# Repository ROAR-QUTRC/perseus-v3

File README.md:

# perseus-v3

The code base for the QUT Robotics Club ROAR teams rover Perseus starting 2026

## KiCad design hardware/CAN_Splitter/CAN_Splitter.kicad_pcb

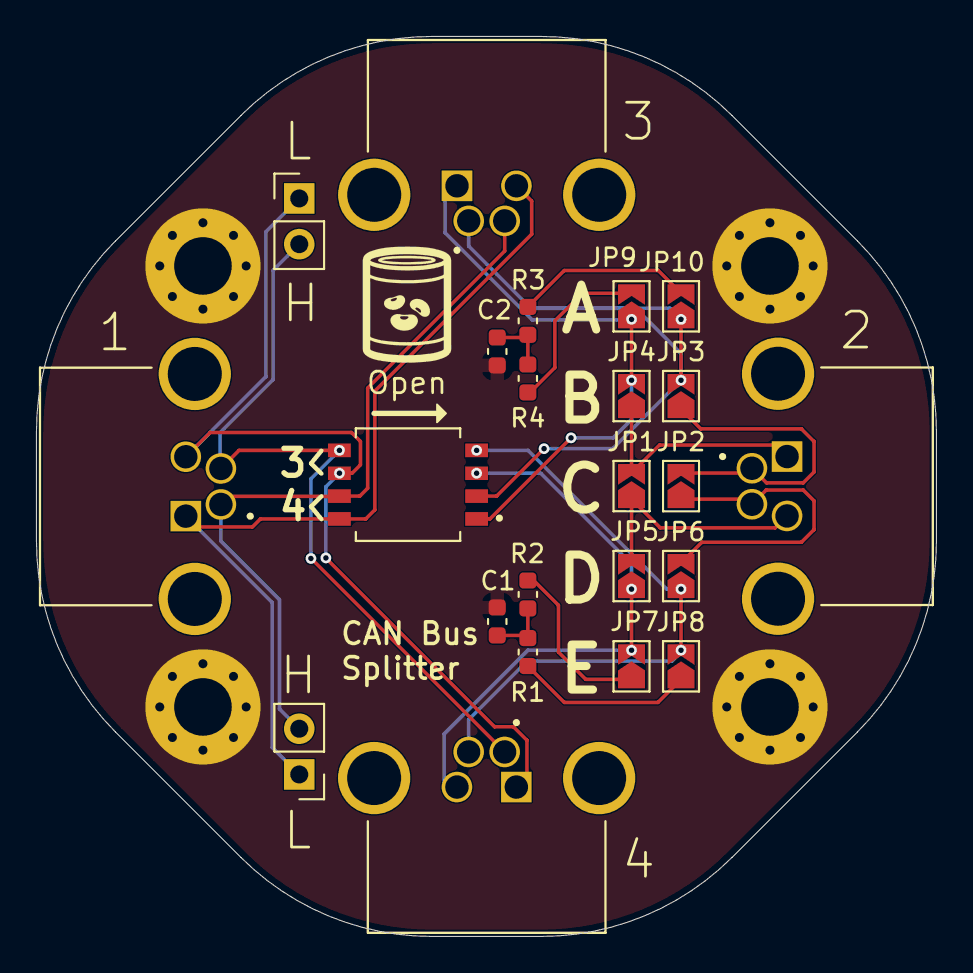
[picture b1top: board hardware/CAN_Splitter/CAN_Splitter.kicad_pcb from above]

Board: 2 copper layers, 50.0 x 50.0 mm, 27 parts (0 on the bottom side), 19 nets.

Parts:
C1, C2: 4.7nF; C_0603_1608Metric
H1, H2, H3, H4: MountingHole_Pad; MountingHole_3.2mm_M3_Pad_Via
J1, J2, J3, J4: 54-00274; TENSILITY_54-00274
J5, J6: Conn_01x02; PinHeader_1x02_P2.54mm_Vertical
JP1, JP2, JP3, JP4, JP5, JP6, JP7, JP8, JP9, JP10: SolderJumper_2_Open; SolderJumper-2_P1.3mm_Open_TrianglePad1.0x1.5mm
R1, R2, R3, R4: 62R; C_0603_1608Metric
SW1: SW_DIP_x04; SW_218-4LPSTR

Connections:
/1 A High: J1.2, J3.4, J5.2, SW1.7
/1 A Low: J1.1, J3.3, J5.1, SW1.8
/1 B High: J1.4, J4.2, J6.2, SW1.5
/1 B Low: J1.3, J4.1, J6.1, SW1.6
/2 A High: J2.2, JP2.2 (B), JP3.1 (A)
/2 A Low: J2.1, JP1.2 (B), JP4.1 (A)
/2 B High: J2.4, JP2.1 (A), JP6.2 (B)
/2 B Low: J2.3, JP1.1 (A), JP5.2 (B)
GND: C1.2, C2.2, H1.1 (1_1), H2.1 (1_1), H3.1 (1_1), H4.1 (1_1)
unnamed: C1.1, R1.1, R2.1
unnamed: C2.1, R3.1, R4.1
unnamed: J3.1, JP4.2 (B), JP9.1 (A), SW1.1
unnamed: J4.3, JP5.1 (A), JP7.2 (B), SW1.3
unnamed: J4.4, JP6.1 (A), JP8.2 (B), SW1.4
unnamed: JP7.1 (A), R2.2
unnamed: JP8.1 (A), R1.2
unnamed: JP9.2 (B), R4.2
unnamed: J3.2, JP3.2 (B), JP10.1 (A), SW1.2
unnamed: JP10.2 (B), R3.2

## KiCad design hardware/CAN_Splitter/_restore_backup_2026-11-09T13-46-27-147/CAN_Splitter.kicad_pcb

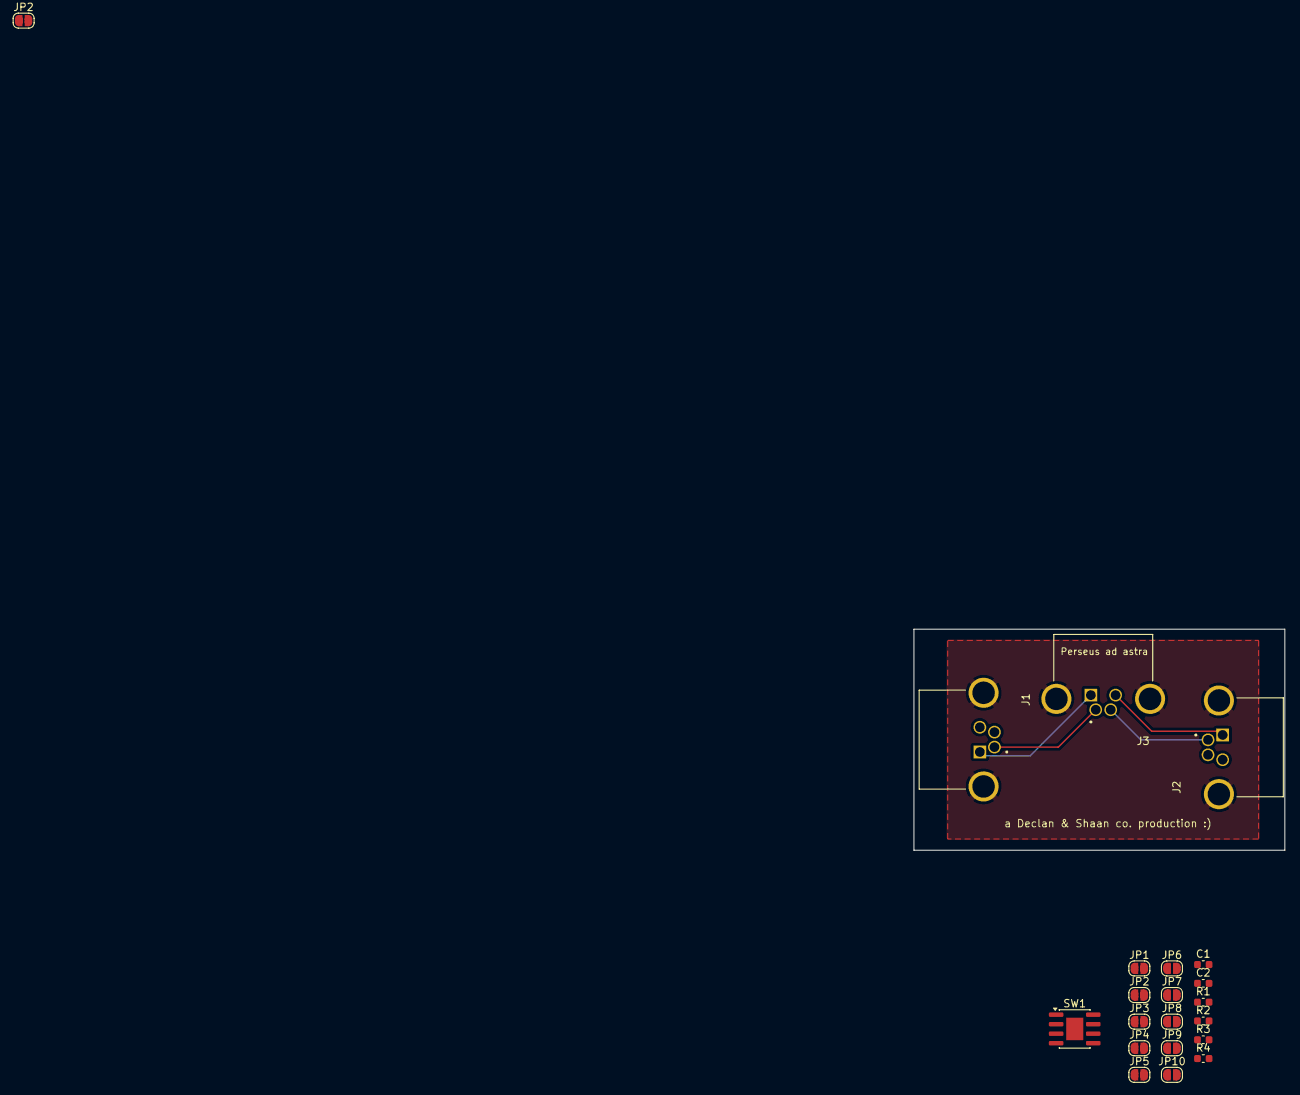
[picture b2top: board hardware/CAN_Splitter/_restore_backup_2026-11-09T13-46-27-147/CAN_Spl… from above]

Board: 2 copper layers, 49.5 x 29.5 mm, 21 parts (0 on the bottom side), 19 nets.

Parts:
C1, C2: 4.7nF; C_0603_1608Metric
J1, J2, J3: 54-00274; TENSILITY_54-00274
JP1, JP2, JP2#2, JP3, JP4, JP5, JP6, JP7, JP8, JP9, JP10: SolderJumper_2_Open; SolderJumper-2_P1.3mm_Open_RoundedPad1.0x1.5mm
R1, R2, R3, R4: 62R; C_0603_1608Metric
SW1: SW_DIP_x04; SOIC-8-1EP_3.9x4.9mm_P1.27mm_EP2.29x3mm

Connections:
/A High: J1.2, J3.4, SW1.2
/A Low: J1.1, J3.3, SW1.1
/B High: J1.4, SW1.4
/B Low: J1.3, SW1.3
GND: C1.2, C2.2, J1.S1 (SHIELD), J1.S2 (SHIELD), J2.S1 (SHIELD), J2.S2 (SHIELD), J3.S1 (SHIELD), J3.S2 (SHIELD)
unnamed: C1.1, R1.1, R2.1
unnamed: C2.1, R3.1, R4.1
unnamed: JP1.1 (A), JP5.1 (A)
unnamed: JP1.2 (B), JP4.1 (A)
unnamed: JP2.1 (A), JP2#2.1 (A), JP6.1 (A)
unnamed: JP2.2 (B), JP2#2.2 (B), JP3.1 (A)
unnamed: J3.1, JP4.2 (B), JP9.2 (B), SW1.8
unnamed: JP5.2 (B), JP7.2 (B), SW1.6
unnamed: JP6.2 (B), JP8.2 (B), SW1.5
unnamed: JP7.1 (A), R2.2
unnamed: JP8.1 (A), R1.2
unnamed: JP9.1 (A), R4.2
unnamed: JP10.1 (A), R3.2
unnamed: J3.2, JP3.2 (B), JP10.2 (B), SW1.7

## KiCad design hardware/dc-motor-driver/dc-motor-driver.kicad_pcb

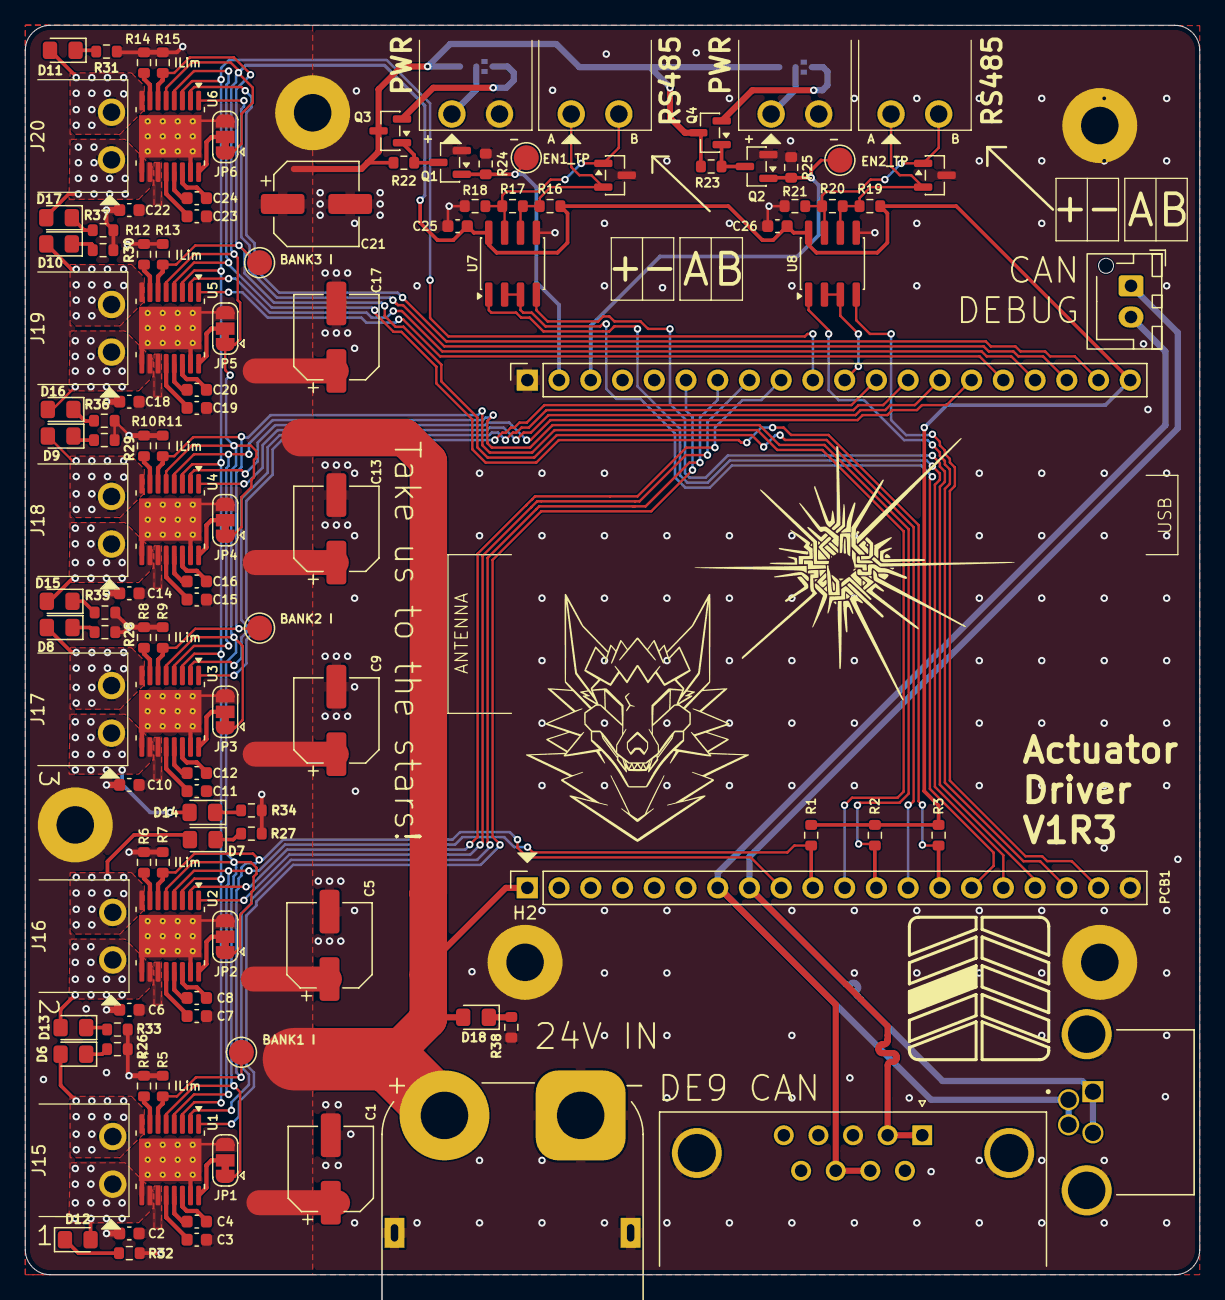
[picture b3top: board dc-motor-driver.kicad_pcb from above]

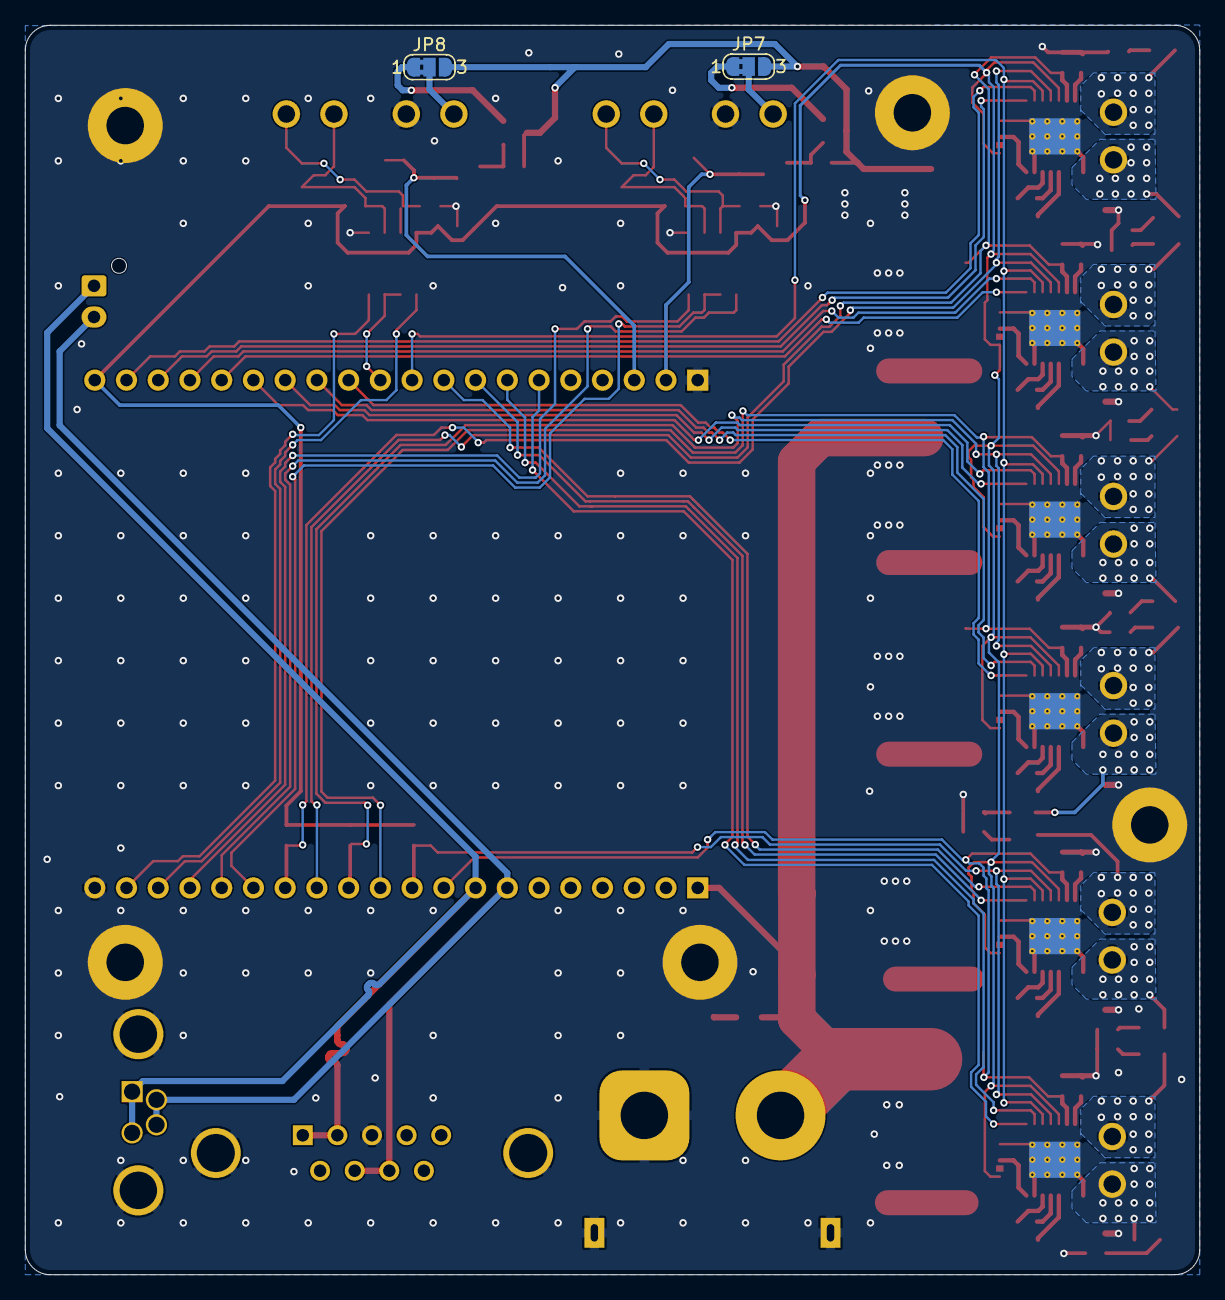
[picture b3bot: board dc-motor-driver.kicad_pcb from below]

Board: 2 copper layers, 94.0 x 100.0 mm, 124 parts (2 on the bottom side), 97 nets.

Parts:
C1, C5, C9, C13, C17, C21: 100u; CP_Elec_6.3x7.7
C2, C3, C6, C7, C10, C11, C14, C15, C18, C19, C22, C23, C25, C26: 100n; C_0603_1608Metric
C4, C8, C12, C16, C20, C24: 22n; C_0603_1608Metric
D1, D2: SM712_SOT23; SOT-23
D6, D7, D8, D9, D10, D11, D12, D13, D14, D15, D16, D17, D18: GREEN; LED_0805_2012Metric_Pad1.15x1.40mm_HandSolder
H1, H2, H3, H4, H5: MountingHole_Pad; MountingHole_3mm_Pad
J1: Tensility_M8_Socket_4P_Shielded_A
J2: VIN; AMASS_XT90PW-M_1x02_P10.90mm_Horizontal
J3: DE9; A-DF_09_A_KG-T2S
J4: Conn_01x02; JST_XH_B2B-XH-AM_1x02_P2.50mm_Vertical
J10, J11, J12, J13, J15, J16, J17, J18, J19, J20: OQ0232510000G; AnyTek_OQ_3.81mm_90_2P_TriangleKeyLock
JP1, JP2, JP3, JP4, JP5, JP6: Jumper_3_Bridged12; SolderJumper-3_P1.3mm_Bridged12_RoundedPad1.0x1.5mm
JP7, JP8: Jumper_3_Bridged12; SolderJumper-3_P1.3mm_Bridged2Bar12_RoundedPad1.0x1.5mm_Num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
PCB1: Smol Brain Board; Smol_Brain_Board
Q1, Q2: 2N7002; SOT-23
Q3, Q4: Si2371EDS; SOT-23
R1, R2, R3, R22, R23, R24, R25, R26, R27, R28, R29, R30, R31, R32, R33, R34, R35, R36, R37, R38: 10k; R_0603_1608Metric
R4, R6, R8, R10, R12, R14: 20k; R_0603_1608Metric
R5, R7, R9, R11, R13, R15: 1k3; R_0603_1608Metric
R16, R18, R19, R21: 330; R_0603_1608Metric
R17, R20: 120; R_0603_1608Metric
TP1, TP2, TP3, TP4, TP5: TestPoint; TestPoint_Pad_D2.0mm
U1, U2, U3, U4, U5, U6: DRV8874PWPR; HTSSOP-16-1EP_4.4x5mm_P0.65mm_EP3.4x5mm_Mask2.66x2.46mm_The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
U7, U8: SP3485CN; SOIC-8_3.9x4.9mm_P1.27mm

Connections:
+3V3: C25.1, C26.1, JP1.1 (A), JP2.1 (A), JP3.1 (A), JP4.1 (A), JP5.1 (A), JP6.1 (A), PCB1.21 (3V3), R1.2, R2.2, R3.2, R16.1, R19.1, U1.5 (VREF), U2.5 (VREF), U3.5 (VREF), U4.5 (VREF), U5.5 (VREF), U6.5 (VREF), U7.8 (VCC), U8.8 (VCC)
/BANK1_I_SENSE: PCB1.9 (A1), R5.1, R7.1, TP1.1 (1_1), U1.6 (IPROPI), U2.6 (IPROPI)
/BANK1_~FLT: PCB1.10 (A2), R1.1, U1.4 (~FAULT), U2.4 (~FAULT)
/BANK2_I_SENSE: PCB1.11 (A3), R9.1, R11.1, TP2.1 (1_1), U3.6 (IPROPI), U4.6 (IPROPI)
/BANK2_~FLT: PCB1.12 (A4), R2.1, U3.4 (~FAULT), U4.4 (~FAULT)
/BANK3_I_SENSE: PCB1.13 (A5), R13.1, R15.1, TP3.1 (1_1), U5.6 (IPROPI), U6.6 (IPROPI)
/BANK3_~FLT: PCB1.14 (A6), R3.1, U5.4 (~FAULT), U6.4 (~FAULT)
/CAN+: J1.2, J1.4, J3.7, J3.8, J4.2, PCB1.7 (CAN_H)
/CAN-: J1.1, J1.3, J3.1, J3.2, J4.1, PCB1.8 (CAN_L)
/ENC_PWR_SW_1: PCB1.39 (I2C_SCK), Q1.1 (G), R24.1, TP4.1 (1_1)
/ENC_PWR_SW_2: PCB1.38 (I2C_SDA), Q2.1 (G), R25.1, TP5.1 (1_1)
/MCU1_DIR: PCB1.15 (A7), U7.2 (~RE), U7.3 (DE)
/MCU1_RX: PCB1.16 (A8), U7.1 (RO)
/MCU1_TX: PCB1.17 (A9), U7.4 (DI)
/MCU2_DIR: PCB1.30 (IO39), U8.2 (~RE), U8.3 (DE)
/MCU2_RX: PCB1.18 (A10), U8.1 (RO)
/MCU2_TX: PCB1.19 (IO12), U8.4 (DI)
/MOT1_IN1: PCB1.35 (IO15), U1.1 (EN_IN1)
/MOT1_IN2: PCB1.34 (IO16), U1.2 (PH_IN2)
/MOT2_IN1: PCB1.33 (IO42), U2.1 (EN_IN1)
/MOT2_IN2: PCB1.32 (IO41), U2.2 (PH_IN2)
/MOT3_IN1: PCB1.29 (IO38), U3.1 (EN_IN1)
/MOT3_IN2: PCB1.28 (IO37), U3.2 (PH_IN2)
/MOT4_IN1: PCB1.27 (IO45), U4.1 (EN_IN1)
/MOT4_IN2: PCB1.26 (IO48), U4.2 (PH_IN2)
/MOT5_IN1: PCB1.25 (IO47), U5.1 (EN_IN1)
/MOT5_IN2: PCB1.24 (IO21), U5.2 (PH_IN2)
/MOT6_IN1: PCB1.23 (IO14), U6.1 (EN_IN1)
/MOT6_IN2: PCB1.22 (IO13), U6.2 (PH_IN2)
/~SLEEP: PCB1.31 (IO40), U1.3 (~SLEEP), U2.3 (~SLEEP), U3.3 (~SLEEP), U4.3 (~SLEEP), U5.3 (~SLEEP), U6.3 (~SLEEP)
GND: C1.2, C2.2, C5.2, C6.2, C9.2, C10.2, C13.2, C14.2, C17.2, C18.2, C21.2, C22.2, C25.2, C26.2, D1.3 (common), D2.3 (common), H1.1 (1_1), H2.1 (1_1), H3.1 (1_1), H4.1 (1_1), H5.1 (1_1), J1.S1 (SHIELD), J1.S2 (SHIELD__1), J2.1 (-), J2.MP, J3.0 (PAD), J3.3, J10.2, J12.2, JP1.3 (B), JP2.3 (B), JP3.3 (B), JP4.3 (B), JP5.3 (B), JP6.3 (B), PCB1.20 (GND), PCB1.40 (GND), Q1.2 (S), Q2.2 (S), R4.2, R5.2, R6.2, R7.2, R8.2, R9.2, R10.2, R11.2, R12.2, R13.2, R14.2, R15.2, R18.2, R21.2, R24.2, R25.2, R26.2, R27.2, R28.2, R29.2, R30.2, R31.2, R32.2, R33.2, R34.2, R35.2, R36.2, R37.2, R38.2, U1.9 (PGND), U1.15 (GND), U1.17 (GND(PAD)), U2.9 (PGND), U2.15 (GND), U2.17 (GND(PAD)), U3.9 (PGND), U3.15 (GND), U3.17 (GND(PAD)), U4.9 (PGND), U4.15 (GND), U4.17 (GND(PAD)), U5.9 (PGND), U5.15 (GND), U5.17 (GND(PAD)), U6.9 (PGND), U6.15 (GND), U6.17 (GND(PAD)), U7.5 (GND), U8.5 (GND)
unnamed: D1.1 (A1), J11.2, R17.2, R18.1, U7.7 (B)
unnamed: D1.2 (A2), J11.1, R16.2, R17.1, U7.6 (A)
unnamed: D2.1 (A1), J13.2, R20.2, R21.1, U8.7 (B)
unnamed: D2.2 (A2), J13.1, R19.2, R20.1, U8.6 (A)
unnamed: D6.2 (A), J15.2, U1.8 (OUT1)
unnamed: D6.1 (K), R26.1
unnamed: D7.2 (A), J16.2, U2.8 (OUT1)
unnamed: D7.1 (K), R27.1
unnamed: D8.2 (A), J17.2, U3.8 (OUT1)
unnamed: D8.1 (K), R28.1
unnamed: D9.2 (A), J18.2, U4.8 (OUT1)
unnamed: D9.1 (K), R29.1
unnamed: D10.2 (A), J19.2, U5.8 (OUT1)
unnamed: D10.1 (K), R30.1
unnamed: D11.2 (A), J20.2, U6.8 (OUT1)
unnamed: D11.1 (K), R31.1
unnamed: D12.2 (A), J15.1, U1.10 (OUT2)
unnamed: D12.1 (K), R32.1
unnamed: D13.2 (A), J16.1, U2.10 (OUT2)
unnamed: D13.1 (K), R33.1
unnamed: D14.2 (A), J17.1, U3.10 (OUT2)
unnamed: D14.1 (K), R34.1
unnamed: D15.2 (A), J18.1, U4.10 (OUT2)
unnamed: D15.1 (K), R35.1
unnamed: D16.2 (A), J19.1, U5.10 (OUT2)
unnamed: D16.1 (K), R36.1
unnamed: D17.2 (A), J20.1, U6.10 (OUT2)
unnamed: D17.1 (K), R37.1
unnamed: D18.1 (K), R38.1
unnamed: J10.1, JP7.2 (C)
unnamed: J12.1, JP8.2 (C)
unnamed: JP1.2 (C), U1.16 (PMODE)
unnamed: JP2.2 (C), U2.16 (PMODE)
unnamed: JP3.2 (C), U3.16 (PMODE)
unnamed: JP4.2 (C), U4.16 (PMODE)
unnamed: JP5.2 (C), U5.16 (PMODE)
unnamed: JP6.2 (C), U6.16 (PMODE)
unnamed: JP7.1 (A), Q3.2 (S)
unnamed: JP8.1 (A), Q4.2 (S)
unnamed: Q1.3 (D), Q3.1 (G), R22.2
unnamed: Q2.3 (D), Q4.1 (G), R23.2
unnamed: C4.1, U1.13 (CPH)
unnamed: C4.2, U1.14 (CPL)
unnamed: R4.1, U1.7 (IMODE)
unnamed: C3.2, U1.12 (VCP)
unnamed: C8.1, U2.13 (CPH)
unnamed: C8.2, U2.14 (CPL)
unnamed: R6.1, U2.7 (IMODE)
unnamed: C7.2, U2.12 (VCP)
unnamed: C12.1, U3.13 (CPH)
unnamed: C12.2, U3.14 (CPL)
unnamed: R8.1, U3.7 (IMODE)
unnamed: C11.2, U3.12 (VCP)
unnamed: C16.1, U4.13 (CPH)
unnamed: C16.2, U4.14 (CPL)
unnamed: R10.1, U4.7 (IMODE)
unnamed: C15.2, U4.12 (VCP)
unnamed: C20.1, U5.13 (CPH)
unnamed: C20.2, U5.14 (CPL)
unnamed: R12.1, U5.7 (IMODE)
unnamed: C19.2, U5.12 (VCP)
unnamed: C24.1, U6.13 (CPH)
unnamed: C24.2, U6.14 (CPL)
unnamed: R14.1, U6.7 (IMODE)
unnamed: C23.2, U6.12 (VCP)
VCC: C1.1, C2.1, C3.1, C5.1, C6.1, C7.1, C9.1, C10.1, C11.1, C13.1, C14.1, C15.1, C17.1, C18.1, C19.1, C21.1, C22.1, C23.1, D18.2 (A), J2.2 (+), JP7.3 (B), JP8.3 (B), PCB1.1 (VCC), Q3.3 (D), Q4.3 (D), R22.1, R23.1, U1.11 (VM), U2.11 (VM), U3.11 (VM), U4.11 (VM), U5.11 (VM), U6.11 (VM)

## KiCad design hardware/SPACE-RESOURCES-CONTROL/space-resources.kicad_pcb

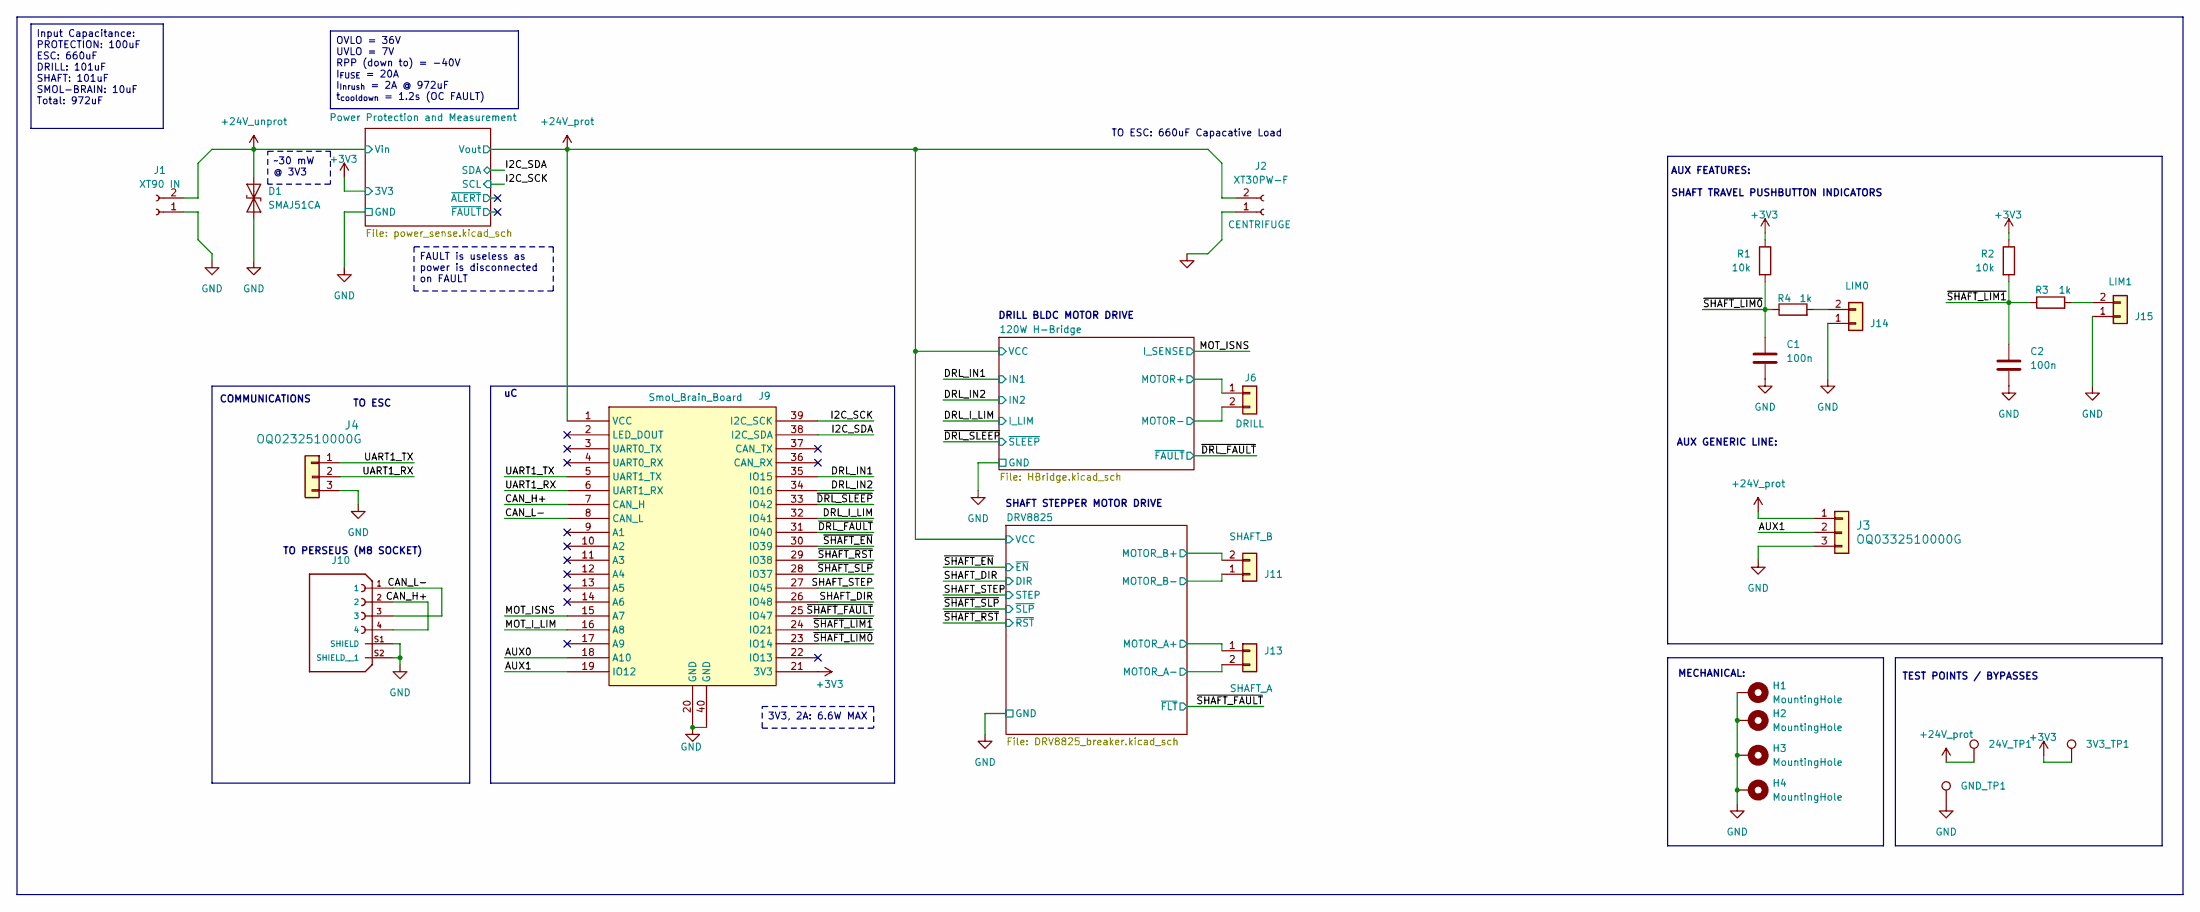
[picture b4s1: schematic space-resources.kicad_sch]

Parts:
3V3_TP1, 24V_TP1: TestPoint; Pin_D0.9mm_L10.0mm_W2.4mm_FlatFork
C1, C2: 100n; C_0603_1608Metric_Pad1.08x0.95mm_HandSolder
D1: SMAJ51CA; D_SMA
GND_TP1: TestPoint; Pin_D0.9mm_L10.0mm_W2.4mm_FlatFork
H1, H2, H3, H4: MountingHole; MountingHole_3.2mm_M3_Pad_Via
J1: XT90 IN; XT90M
J2: XT30PW-F; XT30-PW-F
J3: OQ0332510000G; CONN_OQ0332x0xxxxG_AMP
J4: OQ0232510000G; CONN_OQ0332x0xxxxG_AMP
J6, J11, J13, J14, J15: OQ0232510000G; AnyTek_OQ_3.81mm_90_2P_TriangleKeyLock
J9: Smol_Brain_Board
J10: Tensility_M8_Socket_4P_Shielded_A
R1, R2: 10k; R_0603_1608Metric_Pad0.98x0.95mm_HandSolder
R3, R4: 1k; R_0603_1608Metric_Pad0.98x0.95mm_HandSolder

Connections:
+3V3: 3V3_TP1.1 (1_1), J9.21 (3V3), R1.2, R2.2; also elsewhere on the board
+24V_prot: 24V_TP1.1 (1_1), J2.2, J3.1, J9.1 (VCC); also elsewhere on the board
+24V_unprot: D1.2 (A2), J1.2; also elsewhere on the board
/120W H-Bridge/MOTOR+: J6.1; also elsewhere on the board
/120W H-Bridge/MOTOR-: J6.2; also elsewhere on the board
/AUX0: J9.18 (A10)
/AUX1: J3.2, J9.19 (IO12)
/CAN_H+: J9.7 (CAN_H), J10.2, J10.4
/CAN_L-: J9.8 (CAN_L), J10.1, J10.3
/DRL_IN1: J9.35 (IO15); also elsewhere on the board
/DRL_IN2: J9.34 (IO16); also elsewhere on the board
/DRL_I_LIM: J9.31 (IO40); also elsewhere on the board
/DRV8825/MOTOR_A+: J13.1; also elsewhere on the board
/DRV8825/MOTOR_A-: J13.2; also elsewhere on the board
/DRV8825/MOTOR_B+: J11.2; also elsewhere on the board
/DRV8825/MOTOR_B-: J11.1; also elsewhere on the board
/I2C_SCK: J9.39 (I2C_SCK); also elsewhere on the board
/I2C_SDA: J9.38 (I2C_SDA); also elsewhere on the board
/MOT_ISNS: J9.15 (A7); also elsewhere on the board
/MOT_I_LIM: J9.16 (A8)
/SHAFT_DIR: J9.26 (IO48); also elsewhere on the board
/SHAFT_STEP: J9.27 (IO45); also elsewhere on the board
/UART1_RX: J4.2, J9.6 (UART1_RX)
/UART1_TX: J4.1, J9.5 (UART1_TX)
/~DRL_FAULT: J9.32 (IO41); also elsewhere on the board
/~DRL_SLEEP: J9.33 (IO42); also elsewhere on the board
/~SHAFT_EN: J9.30 (IO39); also elsewhere on the board
/~SHAFT_FAULT: J9.25 (IO47); also elsewhere on the board
/~SHAFT_LIM0: C1.1, J9.23 (IO14), R1.1, R4.2
/~SHAFT_LIM1: C2.1, J9.24 (IO21), R2.1, R3.2
/~SHAFT_RST: J9.29 (IO38); also elsewhere on the board
/~SHAFT_SLP: J9.28 (IO37); also elsewhere on the board
GND: C1.2, C2.2, D1.1 (A1), GND_TP1.1 (1_1), H1.1 (1_1), H2.1 (1_1), H3.1 (1_1), H4.1 (1_1), J1.1, J2.1, J3.3, J4.3, J9.20 (GND), J9.40 (GND), J10.S1 (SHIELD), J10.S2 (SHIELD__1), J14.1, J15.1; also elsewhere on the board
unnamed: J14.2, R4.1
unnamed: J15.2, R3.1

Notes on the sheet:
TO ESC: 660uF Capacative Load
TEST POINTS / BYPASSES
SHAFT STEPPER MOTOR DRIVE
MECHANICAL:
DRILL BLDC MOTOR DRIVE
TO PERSEUS (M8 SOCKET)
COMMUNICATIONS
SHAFT TRAVEL PUSHBUTTON INDICATORS
TO ESC
AUX FEATURES:
AUX GENERIC LINE:
OVLO = 36V UVLO = 7V RPP (down to) = -40V I_{FUSE} = 20A I_{Inrush} = 2A @ 972uF t_{cooldown} = 1.2s (OC FAULT)
FAULT is useless as power is disconnected on FAULT
~30 mW @ 3V3
Input Capacitance: PROTECTION: 100uF ESC: 660uF DRILL: 101uF SHAFT: 101uF SMOL-BRAIN: 10uF Total: 972uF
3V3, 2A: 6.6W MAX

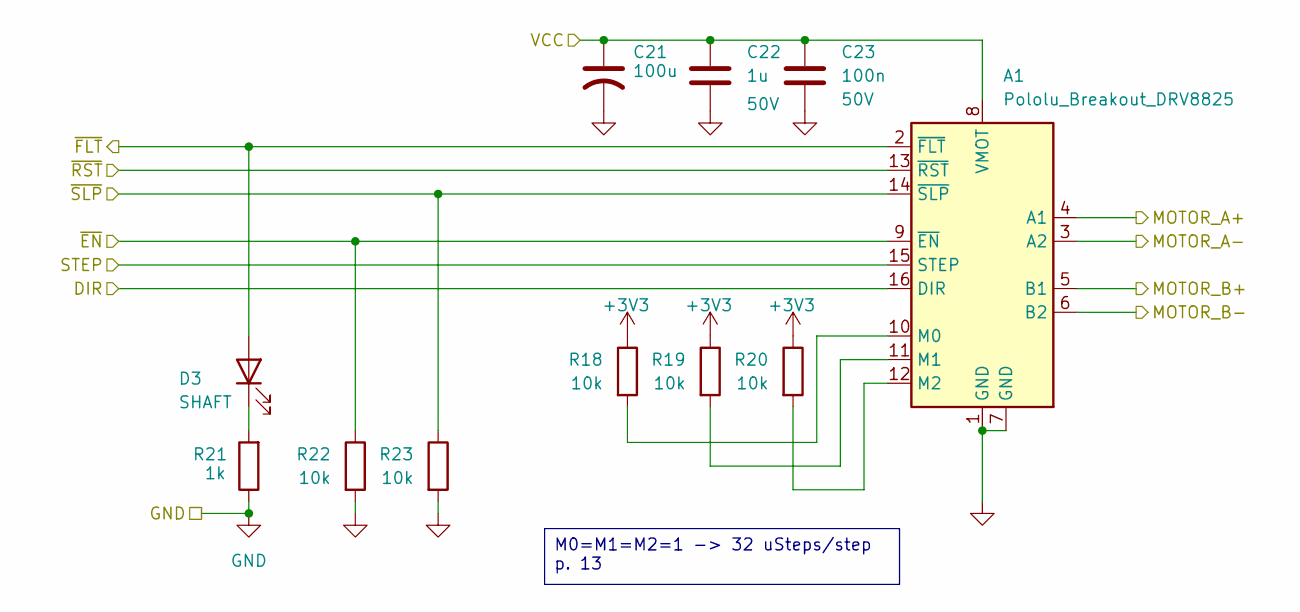
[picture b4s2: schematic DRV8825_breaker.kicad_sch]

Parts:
A1: Pololu_Breakout_DRV8825; Pololu_Breakout-16_15.2x20.3mm
C21: 100u; CP_Elec_6.3x7.7
C22: 1u; C_0603_1608Metric_Pad1.08x0.95mm_HandSolder
C23: 100n; C_0603_1608Metric_Pad1.08x0.95mm_HandSolder
D3: SHAFT; LED_0603_1608Metric_Pad1.05x0.95mm_HandSolder; Part Number LTST-C190GKT
R18, R19, R20, R22, R23: 10k; R_0603_1608Metric_Pad0.98x0.95mm_HandSolder
R21: 1k; R_0603_1608Metric_Pad0.98x0.95mm_HandSolder

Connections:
+3V3: R18.2, R19.2, R20.2; also elsewhere on the board
+24V_prot: A1.8 (VMOT), C21.1, C22.1, C23.1; also elsewhere on the board
/DRV8825/MOTOR_A+: A1.4 (A1); also elsewhere on the board
/DRV8825/MOTOR_A-: A1.3 (A2); also elsewhere on the board
/DRV8825/MOTOR_B+: A1.5 (B1); also elsewhere on the board
/DRV8825/MOTOR_B-: A1.6 (B2); also elsewhere on the board
/SHAFT_DIR: A1.16 (DIR); also elsewhere on the board
/SHAFT_STEP: A1.15 (STEP); also elsewhere on the board
/~SHAFT_EN: A1.9 (~EN), R22.2; also elsewhere on the board
/~SHAFT_FAULT: A1.2 (~FLT), D3.2 (A); also elsewhere on the board
/~SHAFT_RST: A1.13 (~RST); also elsewhere on the board
/~SHAFT_SLP: A1.14 (~SLP), R23.2; also elsewhere on the board
GND: A1.1 (GND), A1.7 (GND), C21.2, C22.2, C23.2, R21.2, R22.1, R23.1; also elsewhere on the board
unnamed: A1.10 (M0), R18.1
unnamed: A1.11 (M1), R19.1
unnamed: A1.12 (M2), R20.1
unnamed: D3.1 (K), R21.1

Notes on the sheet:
M0=M1=M2=1 -> 32 uSteps/step p. 13

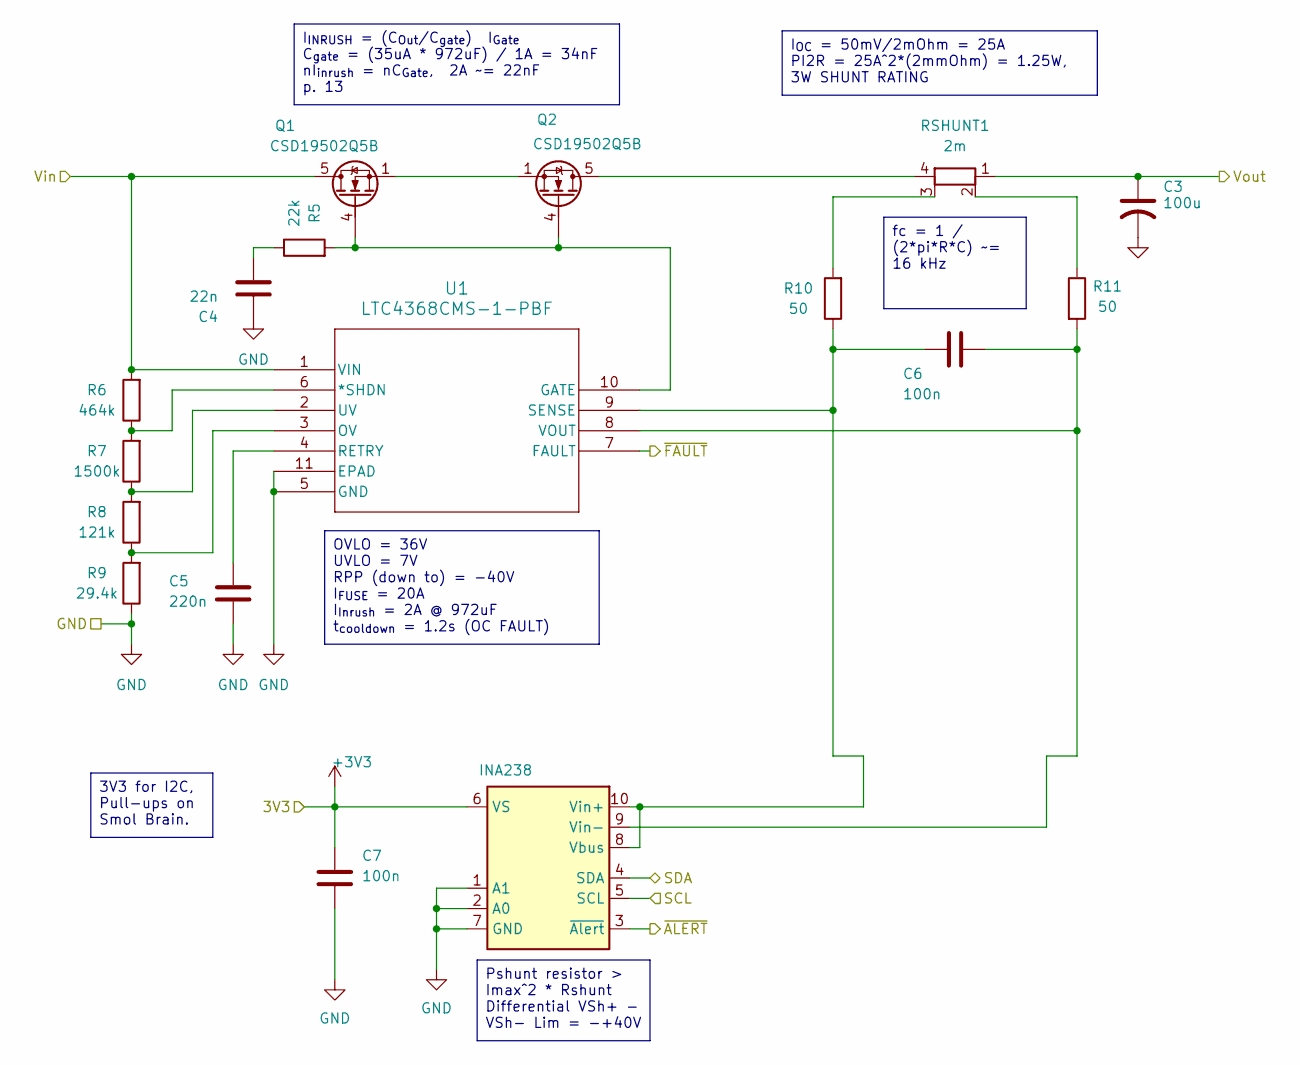
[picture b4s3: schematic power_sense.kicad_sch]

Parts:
C3: 100u; CP_Elec_6.3x7.7
C4: 22n; C_0603_1608Metric_Pad1.08x0.95mm_HandSolder
C5: 220n; C_0603_1608Metric_Pad1.08x0.95mm_HandSolder
C6, C7: 100n; C_0603_1608Metric_Pad1.08x0.95mm_HandSolder
Q1, Q2: CSD19502Q5B; TDSON-8-1; JLCPCB Part # C2864118
R5: 22k; R_0603_1608Metric_Pad0.98x0.95mm_HandSolder
R6: 464k; R_0603_1608Metric_Pad0.98x0.95mm_HandSolder
R7: 1500k; R_0603_1608Metric_Pad0.98x0.95mm_HandSolder
R8: 121k; R_0603_1608Metric_Pad0.98x0.95mm_HandSolder
R9: 29.4k; R_0603_1608Metric_Pad0.98x0.95mm_HandSolder
R10, R11: 50; R_0603_1608Metric_Pad0.98x0.95mm_HandSolder
RSHUNT1: 2m; SMT_61L000FEA_VIS
U1: LTC4368CMS-1-PBF; MS_10_ADI
U2: INA238; TSSOP-10_3x3mm_P0.5mm

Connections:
+3V3: C7.1, U2.6 (VS); also elsewhere on the board
+24V_prot: C3.1, RSHUNT1.1; also elsewhere on the board
+24V_unprot: Q1.5 (D), R6.2, U1.1 (VIN); also elsewhere on the board
/I2C_SCK: U2.5 (SCL); also elsewhere on the board
/I2C_SDA: U2.4 (SDA); also elsewhere on the board
/Power Protection and Measurement/~ALERT: U2.3 (~Alert)
/Power Protection and Measurement/~FAULT: U1.7 (FAULT)
GND: C3.2, C4.1, C5.2, C7.2, R9.1, U1.5 (GND), U1.11 (EPAD), U2.1 (A1), U2.2 (A0), U2.7 (GND); also elsewhere on the board
unnamed: C4.2, R5.1
unnamed: Q1.4 (G), Q2.4 (G), R5.2, U1.10 (GATE)
unnamed: Q1.1 (S), Q1.2 (S), Q1.3 (S), Q2.1 (S), Q2.2 (S), Q2.3 (S)
unnamed: Q2.5 (D), RSHUNT1.4
unnamed: R10.2, RSHUNT1.3
unnamed: R11.1, RSHUNT1.2
unnamed: R6.1, R7.2, U1.6 (*SHDN)
unnamed: R8.1, R9.2, U1.3 (OV)
unnamed: C5.1, U1.4 (RETRY)
unnamed: C6.1, R10.1, U1.9 (SENSE), U2.8 (Vbus), U2.10 (Vin+)
unnamed: R7.1, R8.2, U1.2 (UV)
unnamed: C6.2, R11.2, U1.8 (VOUT), U2.9 (Vin-)

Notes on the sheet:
Pshunt resistor > Imax^2 * Rshunt Differential VSh+ - VSh- Lim = -+40V
3V3 for I2C, Pull-ups on Smol Brain.
fc = 1 / (2*pi*R*C) ~= 16 kHz
OVLO = 36V UVLO = 7V RPP (down to) = -40V I_{FUSE} = 20A I_{Inrush} = 2A @ 972uF t_{cooldown} = 1.2s (OC FAULT)
I_{INRUSH} = (C_{Out}/C_{gate}) I_{Gate} C_{gate} = (35uA * 972uF) / 1A = 34nF nI_{inrush} = nC_{Gate}, 2A ~= 22nF p. 13
I_{OC} = 50mV/2mOhm = 25A PI2R = 25A^2*(2mmOhm) = 1.25W, 3W SHUNT RATING

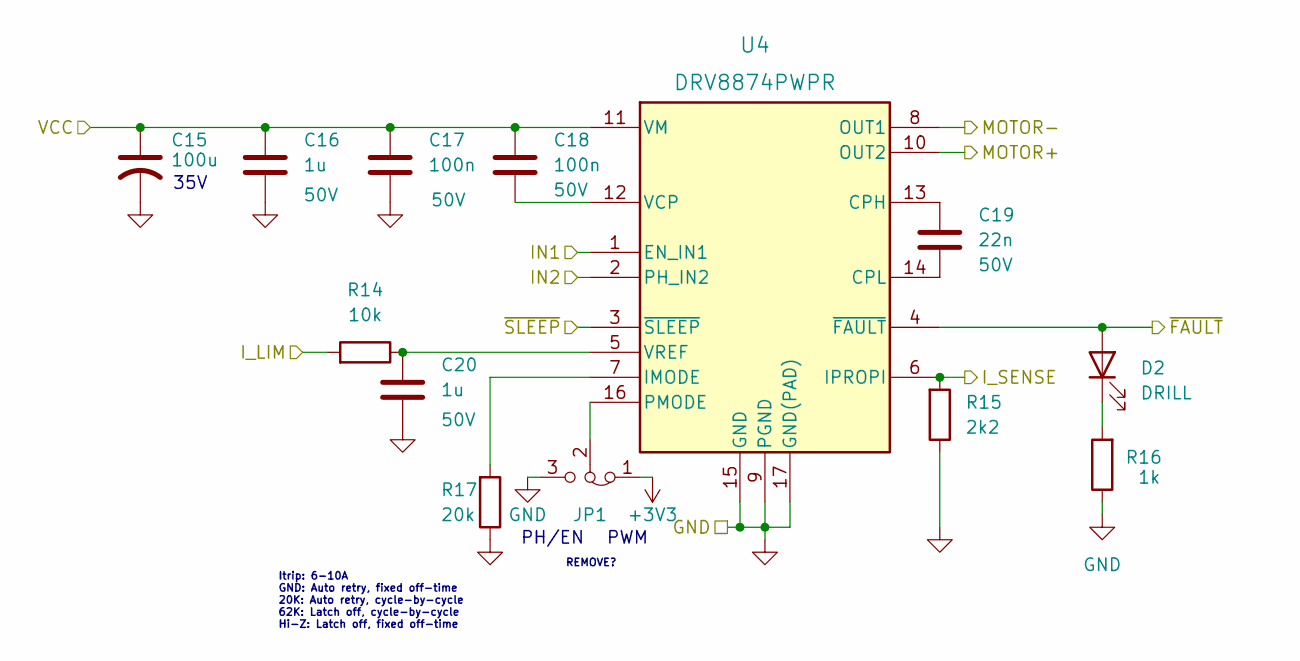
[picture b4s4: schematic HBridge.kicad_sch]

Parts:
C15: 100u; CP_Elec_6.3x7.7
C16, C20: 1u; C_0603_1608Metric_Pad1.08x0.95mm_HandSolder
C17, C18: 100n; C_0603_1608Metric_Pad1.08x0.95mm_HandSolder
C19: 22n; C_0603_1608Metric_Pad1.08x0.95mm_HandSolder
D2: DRILL; LED_0603_1608Metric_Pad1.05x0.95mm_HandSolder; Part Number LTST-C190GKT
JP1: Jumper_3_Bridged12; SolderJumper-3_P1.3mm_Bridged12_RoundedPad1.0x1.5mm
R14: 10k; R_0603_1608Metric_Pad0.98x0.95mm_HandSolder
R15: 2k2; R_0603_1608Metric_Pad0.98x0.95mm_HandSolder
R16: 1k; R_0603_1608Metric_Pad0.98x0.95mm_HandSolder
R17: 20k; R_0603_1608Metric_Pad0.98x0.95mm_HandSolder
U4: DRV8874PWPR; PWP0016J_N

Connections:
+3V3: JP1.1 (A); also elsewhere on the board
+24V_prot: C15.1, C16.1, C17.1, C18.1, U4.11 (VM); also elsewhere on the board
/120W H-Bridge/MOTOR+: U4.10 (OUT2); also elsewhere on the board
/120W H-Bridge/MOTOR-: U4.8 (OUT1); also elsewhere on the board
/DRL_IN1: U4.1 (EN_IN1); also elsewhere on the board
/DRL_IN2: U4.2 (PH_IN2); also elsewhere on the board
/DRL_I_LIM: R14.1; also elsewhere on the board
/MOT_ISNS: R15.1, U4.6 (IPROPI); also elsewhere on the board
/~DRL_FAULT: D2.2 (A), U4.4 (~FAULT); also elsewhere on the board
/~DRL_SLEEP: U4.3 (~SLEEP); also elsewhere on the board
GND: C15.2, C16.2, C17.2, C20.2, JP1.3 (B), R15.2, R16.2, R17.2, U4.9 (PGND), U4.15 (GND), U4.17 (GND(PAD)); also elsewhere on the board
unnamed: D2.1 (K), R16.1
unnamed: JP1.2 (C), U4.16 (PMODE)
unnamed: C19.1, U4.13 (CPH)
unnamed: C19.2, U4.14 (CPL)
unnamed: R17.1, U4.7 (IMODE)
unnamed: C18.2, U4.12 (VCP)
unnamed: C20.1, R14.2, U4.5 (VREF)

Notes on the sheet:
PWM
REMOVE?
35V
Itrip: 6-10A GND: Auto retry, fixed off-time 20K: Auto retry, cycle-by-cycle 62K: Latch off, cycle-by-cycle Hi-Z: Latch off, fixed off-time
PH/EN

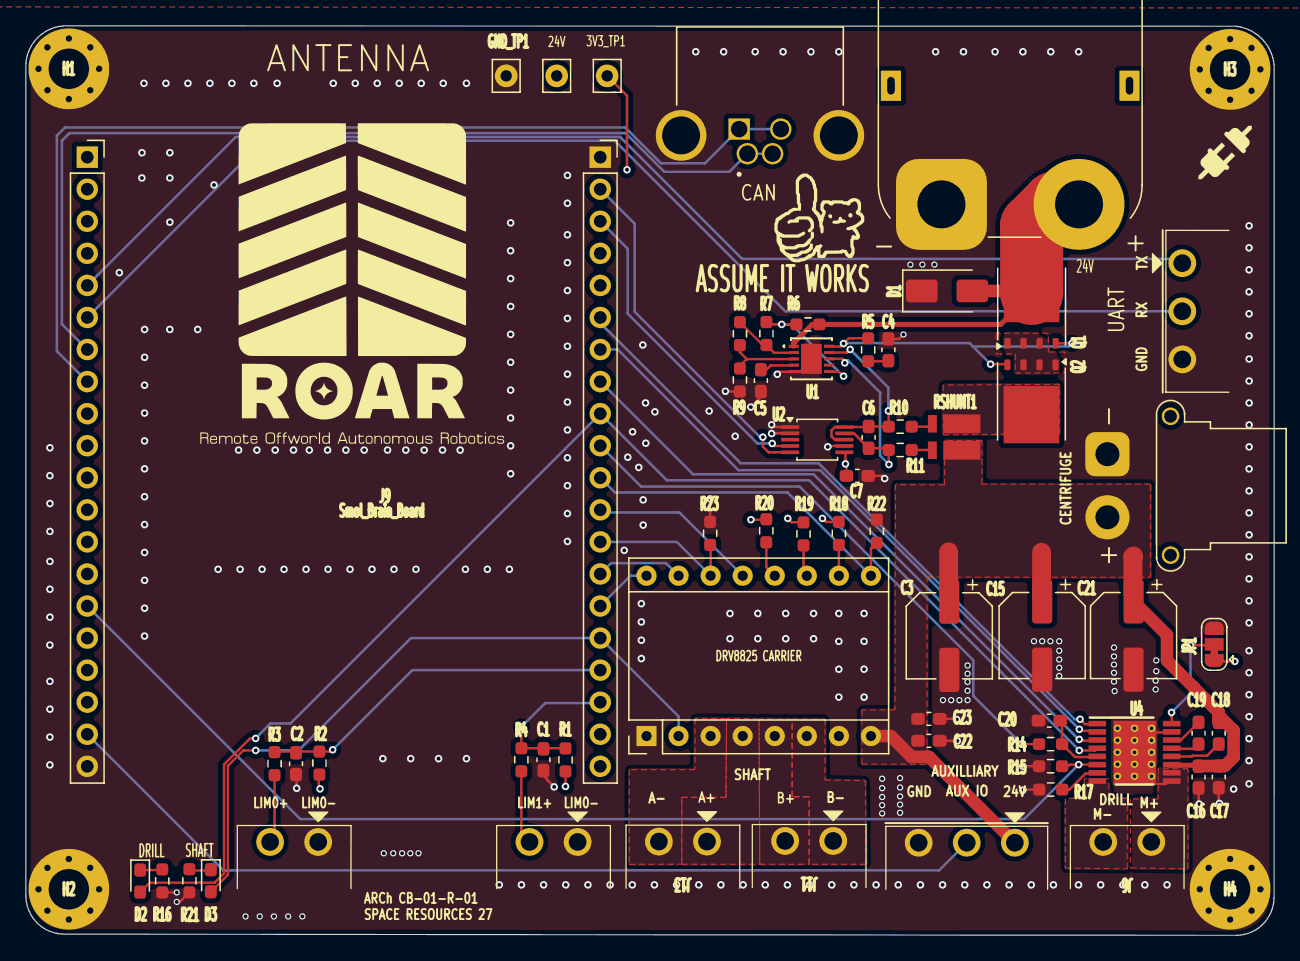
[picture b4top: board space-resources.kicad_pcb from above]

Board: 4 copper layers, 98.9 x 72.0 mm, 66 parts (0 on the bottom side), 56 nets.

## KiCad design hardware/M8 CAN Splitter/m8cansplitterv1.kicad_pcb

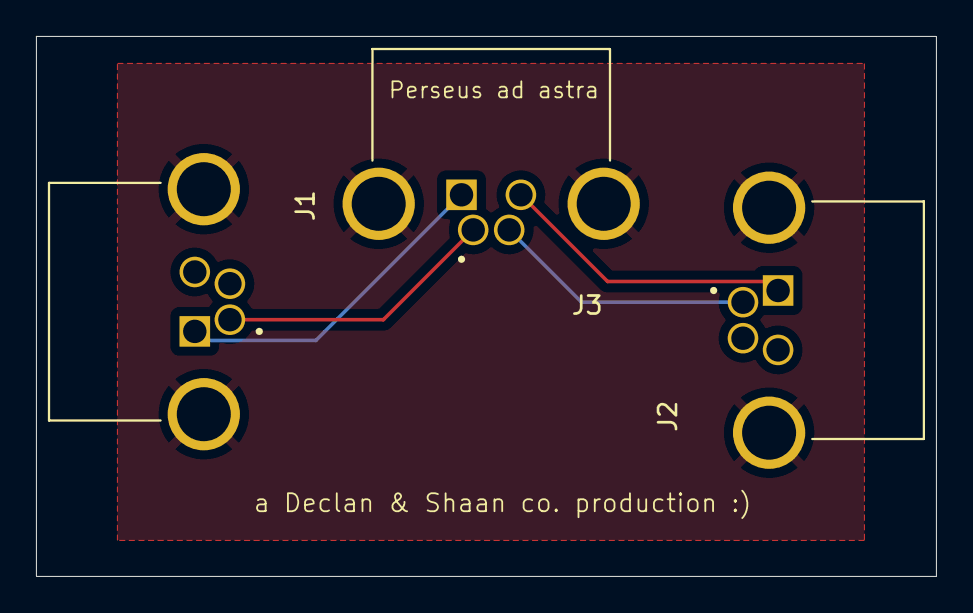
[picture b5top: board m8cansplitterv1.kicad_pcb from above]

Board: 2 copper layers, 50.0 x 30.0 mm, 3 parts (0 on the bottom side), 5 nets.

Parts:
J1, J2, J3: 54-00274; TENSILITY_54-00274

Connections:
/CAN A HI: J1.1, J3.1
/CAN A LOW: J1.2, J3.2
/CAN B HI: J2.1, J3.3
/CAN B LOW: J2.2, J3.4
GND: J1.S1 (SHIELD), J1.S2 (SHIELD), J2.S1 (SHIELD), J2.S2 (SHIELD), J3.S1 (SHIELD), J3.S2 (SHIELD)
